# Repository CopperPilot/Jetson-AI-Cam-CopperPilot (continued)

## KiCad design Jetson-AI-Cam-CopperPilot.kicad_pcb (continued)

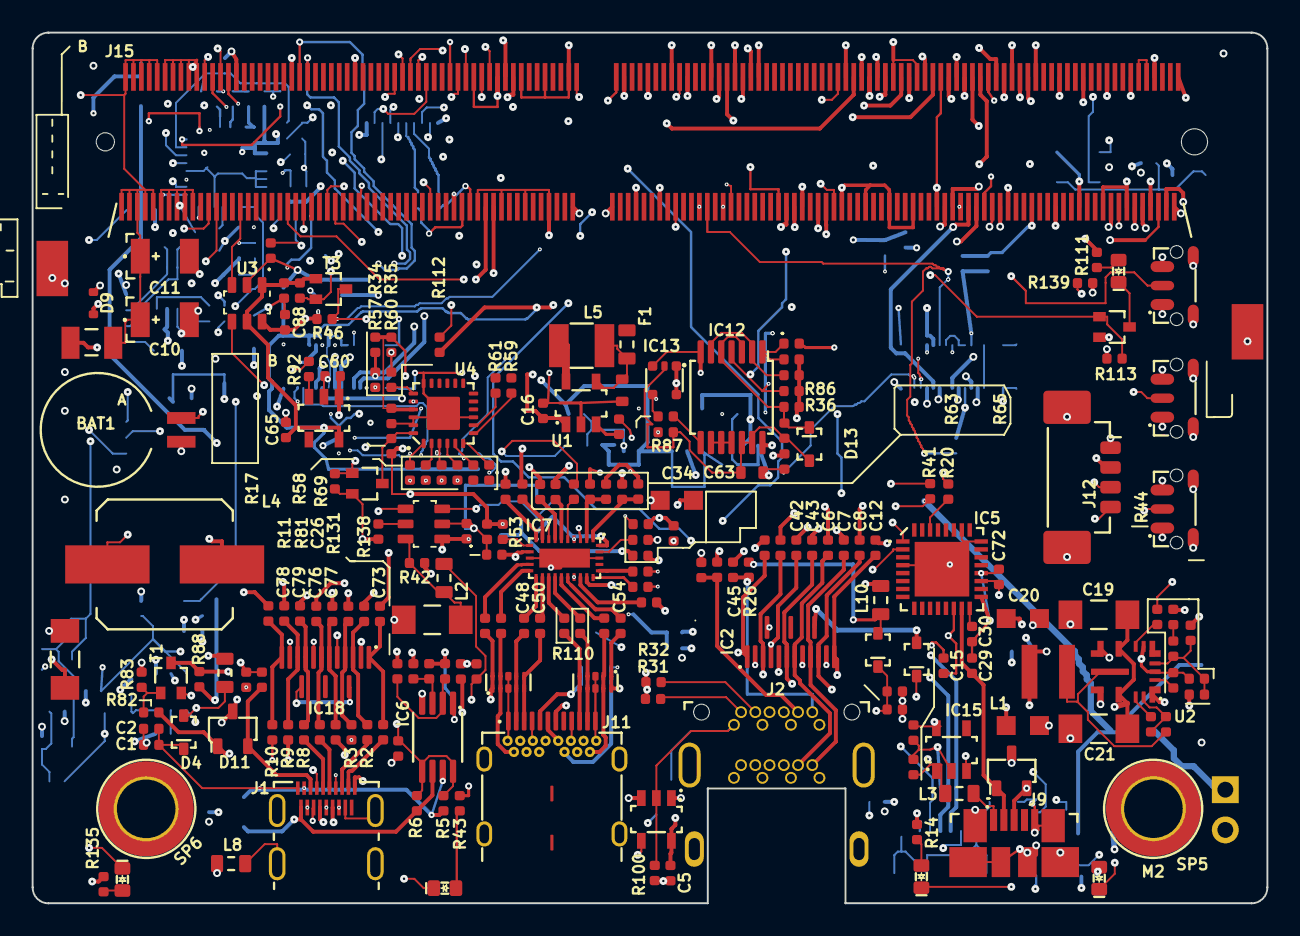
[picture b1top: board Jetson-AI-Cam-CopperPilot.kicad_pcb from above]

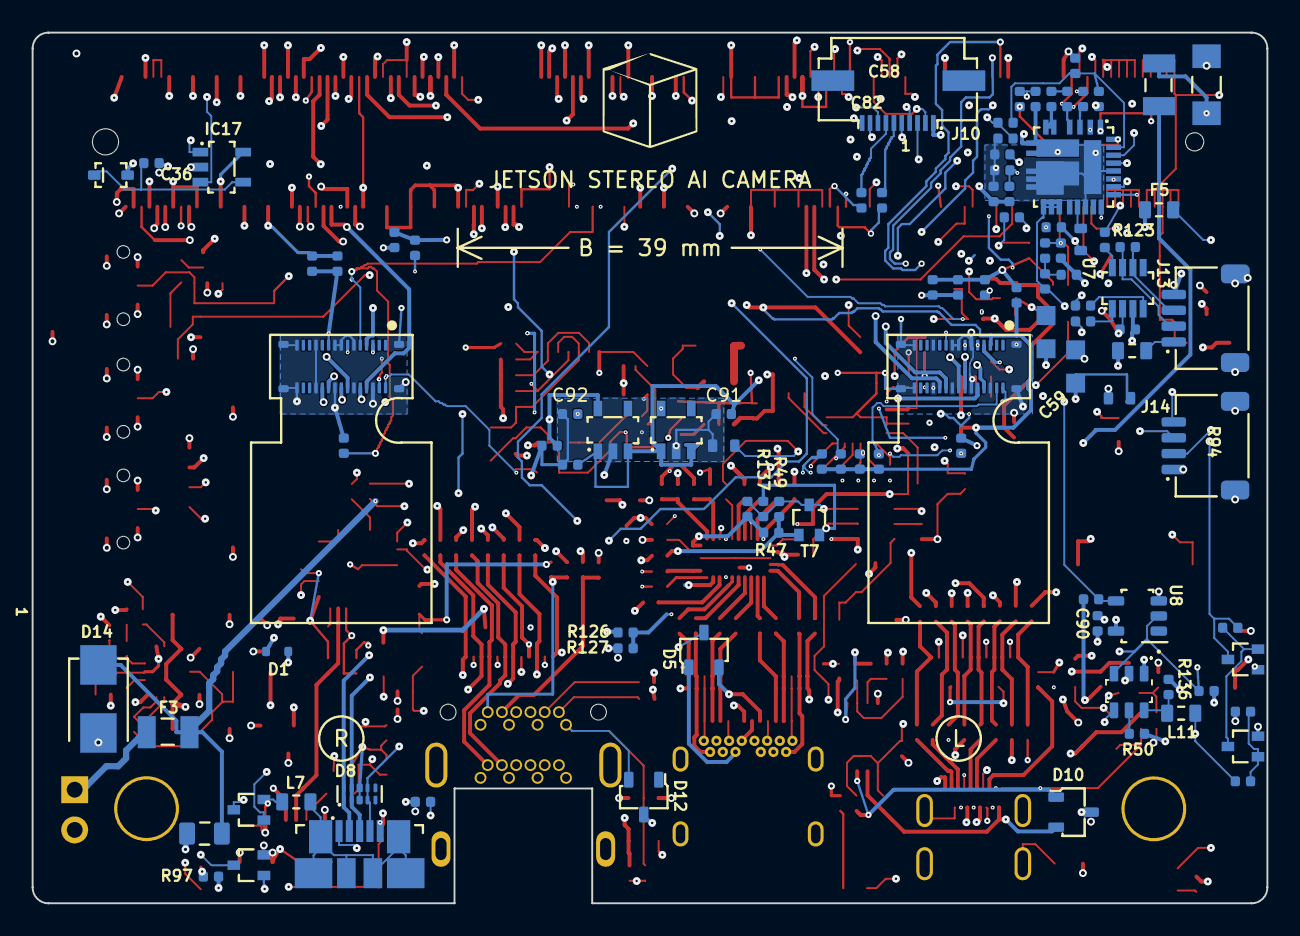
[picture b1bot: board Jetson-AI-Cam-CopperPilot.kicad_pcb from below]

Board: 8 copper layers, 78.0 x 55.0 mm, 305 parts (99 on the bottom side), 254 nets.

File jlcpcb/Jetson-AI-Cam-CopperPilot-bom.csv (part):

Designator,Value,Footprint,LCSC,MPN,DNP
BOOT1,LED_G_0603_LG_L29K-G2J1-24-Z,jetson-footprints:LED_0603_1608Metric_G,C72043,LG L29K-G2J1-24-Z,
C1,C_4u7_0402,jetson-footprints:C_0402_1005Metric,C23733,GRM155R61A475MEAAD,
C2,C_4u7_0402,jetson-footprints:C_0402_1005Metric,C23733,GRM155R61A475MEAAD,
C3,C_4u7_0402,jetson-footprints:C_0402_1005Metric,C23733,GRM155R61A475MEAAD,
C4,C_4u7_0402,jetson-footprints:C_0402_1005Metric,C23733,GRM155R61A475MEAAD,
C5,C_100n_0402,jetson-footprints:C_0402_1005Metric,C1525,GRM155R61H104KE14D,
C6,C_100n_0402,jetson-footprints:C_0402_1005Metric,C1525,GRM155R61H104KE14D,
C7,C_100n_0402,jetson-footprints:C_0402_1005Metric,C1525,GRM155R61H104KE14D,
C8,C_100n_0402,jetson-footprints:C_0402_1005Metric,C1525,GRM155R61H104KE14D,
C9,C_100n_0402,jetson-footprints:C_0402_1005Metric,C1525,GRM155R61H104KE14D,
C10,C_Pol_330u_6.3V_KEMET-T520-B,jetson-footprints:C_Pol_EIA-B,C134785,T520B337M006ATE040,
C11,C_Pol_330u_6.3V_KEMET-T520-B,jetson-footprints:C_Pol_EIA-B,C134785,T520B337M006ATE040,
C12,C_100n_0402,jetson-footprints:C_0402_1005Metric,C1525,GRM155R61H104KE14D,
C13,C_100n_0402,jetson-footprints:C_0402_1005Metric,C1525,GRM155R61H104KE14D,
C15,C_47p_0402,jetson-footprints:C_0402_1005Metric,C1548,C0402C470J5GACTU,
C17,C_10u_1206_50V,jetson-footprints:C_1206_3216Metric,C13585,C3216X7R1H106K160AE,
C19,C_10u_1206_50V,jetson-footprints:C_1206_3216Metric,C13585,C3216X7R1H106K160AE,
C20,C_47u_0805,jetson-footprints:C_0805_2012Metric,C16780,C0805C476M9PACTU,
C21,C_10u_1206_50V,jetson-footprints:C_1206_3216Metric,C13585,C3216X7R1H106K160AE,
C22,C_10u_1206_50V,jetson-footprints:C_1206_3216Metric,C13585,C3216X7R1H106K160AE,
C24,C_6p_0402,jetson-footprints:C_0402_1005Metric,C1571,0402N6R0D500CT,
C25,C_10u_0805,jetson-footprints:C_0805_2012Metric,C15850,160R15X106KV4E,
C26,C_100n_0402,jetson-footprints:C_0402_1005Metric,C1525,GRM155R61H104KE14D,
C27,C_100n_0402,jetson-footprints:C_0402_1005Metric,C1525,GRM155R61H104KE14D,
C29,C_47p_0402,jetson-footprints:C_0402_1005Metric,C1548,C0402C470J5GACTU,
C30,C_100n_0402,jetson-footprints:C_0402_1005Metric,C1525,GRM155R61H104KE14D,
C31,C_100u_1206,jetson-footprints:C_1206_3216Metric,C15068,GRM31CR60J107MEA8K,
C32,C_10u_0402,jetson-footprints:C_0402_1005Metric,C15525,CC0402MRX5R5BB106,
C33,C_100n_0402,jetson-footprints:C_0402_1005Metric,C1525,GRM155R61H104KE14D,
C34,C_47u_0805,jetson-footprints:C_0805_2012Metric,C16780,C0805C476M9PACTU,
C35,C_10u_0603,jetson-footprints:C_0603_1608Metric,C19702,GRM188R61A106KE69D,
C36,C_100n_0402,jetson-footprints:C_0402_1005Metric,C1525,GRM155R61H104KE14D,
C39,C_100n_0402,jetson-footprints:C_0402_1005Metric,C1525,GRM155R61H104KE14D,
C40,C_100n_0402,jetson-footprints:C_0402_1005Metric,C1525,GRM155R61H104KE14D,
C41,C_47n_0402,jetson-footprints:C_0402_1005Metric,C1536,GRM155R71C473KA01D,
C42,C_100n_0402,jetson-footprints:C_0402_1005Metric,C1525,GRM155R61H104KE14D,
C43,C_100n_0402,jetson-footprints:C_0402_1005Metric,C1525,GRM155R61H104KE14D,
C44,C_100n_0402,jetson-footprints:C_0402_1005Metric,C1525,GRM155R61H104KE14D,
C45,C_100n_0402,jetson-footprints:C_0402_1005Metric,C1525,GRM155R61H104KE14D,
C48,C_100n_0402,jetson-footprints:C_0402_1005Metric,C1525,GRM155R61H104KE14D,
C50,C_100n_0402,jetson-footprints:C_0402_1005Metric,C1525,GRM155R61H104KE14D,
C53,C_100n_0402,jetson-footprints:C_0402_1005Metric,C1525,GRM155R61H104KE14D,
C54,C_100n_0402,jetson-footprints:C_0402_1005Metric,C1525,GRM155R61H104KE14D,
C56,C_100n_50V_0402,jetson-footprints:C_0402_1005Metric,C307331,GRM155R71H104KE14D,
C57,C_100n_0402,jetson-footprints:C_0402_1005Metric,C1525,GRM155R61H104KE14D,
C58,C_33n_0402,jetson-footprints:C_0402_1005Metric,C1533,GCM155R71E333KA55D,
C59,C_47u_0805,jetson-footprints:C_0805_2012Metric,C16780,C0805C476M9PACTU,
C60,C_2u2_0402,jetson-footprints:C_0402_1005Metric,C12530,C1005X5R1A225K050BC,
C62,C_4u7_0402,jetson-footprints:C_0402_1005Metric,C23733,GRM155R61A475MEAAD,
C63,C_10u_0603,jetson-footprints:C_0603_1608Metric,C19702,GRM188R61A106KE69D,
C64,C_47u_0805,jetson-footprints:C_0805_2012Metric,C16780,C0805C476M9PACTU,
C65,C_1u_0402,jetson-footprints:C_0402_1005Metric,C52923,C1005X6S1A105K050BC,
C66,C_1u_0402,jetson-footprints:C_0402_1005Metric,C52923,C1005X6S1A105K050BC,
C67,C_2u2_0402,jetson-footprints:C_0402_1005Metric,C12530,C1005X5R1A225K050BC,
C71,C_100n_0402,jetson-footprints:C_0402_1005Metric,C1525,GRM155R61H104KE14D,
C72,C_100n_0402,jetson-footprints:C_0402_1005Metric,C1525,GRM155R61H104KE14D,
C73,C_100n_0402,jetson-footprints:C_0402_1005Metric,C1525,GRM155R61H104KE14D,
C74,C_100n_0402,jetson-footprints:C_0402_1005Metric,C1525,GRM155R61H104KE14D,
C75,C_100n_0402,jetson-footprints:C_0402_1005Metric,C1525,GRM155R61H104KE14D,
C76,C_100n_0402,jetson-footprints:C_0402_1005Metric,C1525,GRM155R61H104KE14D,
C77,C_100n_0402,jetson-footprints:C_0402_1005Metric,C1525,GRM155R61H104KE14D,
C78,C_100n_0402,jetson-footprints:C_0402_1005Metric,C1525,GRM155R61H104KE14D,
C79,C_100n_0402,jetson-footprints:C_0402_1005Metric,C1525,GRM155R61H104KE14D,
C80,C_100n_0402,jetson-footprints:C_0402_1005Metric,C1525,GRM155R61H104KE14D,
C81,C_10u_0603,jetson-footprints:C_0603_1608Metric,C19702,GRM188R61A106KE69D,
C83,C_100n_0402,jetson-footprints:C_0402_1005Metric,C1525,GRM155R61H104KE14D,
C84,C_1u_0402,jetson-footprints:C_0402_1005Metric,C52923,C1005X6S1A105K050BC,
C85,C_4u7_0603,jetson-footprints:C_0603_1608Metric,C19666,C1608X5R1V475M080AC,
C86,C_100n_0402,jetson-footprints:C_0402_1005Metric,C1525,GRM155R61H104KE14D,
C87,C_1u_0402,jetson-footprints:C_0402_1005Metric,C52923,C1005X6S1A105K050BC,
C88,C_100n_0402,jetson-footprints:C_0402_1005Metric,C1525,GRM155R61H104KE14D,
C89,C_100n_0402,jetson-footprints:C_0402_1005Metric,C1525,GRM155R61H104KE14D,
C90,C_100n_0402,jetson-footprints:C_0402_1005Metric,C1525,GRM155R61H104KE14D,
C91,1uF_0402,jetson-footprints:C_0402_1005Metric,C52923,C1005X6S1A105K050BC,
C92,2.2uF_0402,jetson-footprints:C_0402_1005Metric,C12530,C1005X5R1A225K050BC,
C93,1uF_0402,jetson-footprints:C_0402_1005Metric,C52923,C1005X6S1A105K050BC,
C94,2.2uF_0402,jetson-footprints:C_0402_1005Metric,C12530,C1005X5R1A225K050BC,
C95,C_100n_0402,jetson-footprints:C_0402_1005Metric,C1525,GRM155R61H104KE14D,
C96,C_100n_0402,jetson-footprints:C_0402_1005Metric,C1525,GRM155R61H104KE14D,
C97,C_100n_0402,jetson-footprints:C_0402_1005Metric,C1525,GRM155R61H104KE14D,
C98,C_2u2_0402,jetson-footprints:C_0402_1005Metric,C12530,C1005X5R1A225K050BC,
C99,C_100n_0402,jetson-footprints:C_0402_1005Metric,C1525,GRM155R61H104KE14D,
C100,C_100n_0402,jetson-footprints:C_0402_1005Metric,C1525,GRM155R61H104KE14D,
C101,C_100n_0402,jetson-footprints:C_0402_1005Metric,C1525,GRM155R61H104KE14D,
C102,C_2u2_0402,jetson-footprints:C_0402_1005Metric,C12530,C1005X5R1A225K050BC,
C103,C_100n_0402,jetson-footprints:C_0402_1005Metric,C1525,GRM155R61H104KE14D,
C104,C_100n_0402,jetson-footprints:C_0402_1005Metric,C1525,GRM155R61H104KE14D,
CAM_L,IMX219_30P,jetson-footprints:Camera_Module_IMX219-D160,C424662,BM20B(0.8)-30DS-0.4V(51),
CAM_R,IMX219_30P,jetson-footprints:Camera_Module_IMX219-D160,C424662,BM20B(0.8)-30DS-0.4V(51),
D1,ESD5B5_0ST1G,jetson-footprints:SOD-523_NP,C15906,ESD5B5.0ST1G,
D2,B0520W,jetson-footprints:D_SOD-323F,C8598,B0520W,
D3,PESD2USB5UV-TR,jetson-footprints:SOT-23-3,C2827695,PESD2USB5UV-TR,
D4,B0520W,jetson-footprints:D_SOD-323F,C8598,B0520W,
D5,PESD2USB5UV-TR,jetson-footprints:SOT-23-3,C2827695,PESD2USB5UV-TR,
D6,TPD4E05U06QDQARQ1,jetson-footprints:USON-10_2.5x1mm_P0.5mm,C138252,TPD4E05U06QDQARQ1,
D7,TPD4E05U06QDQARQ1,jetson-footprints:USON-10_2.5x1mm_P0.5mm,C138252,TPD4E05U06QDQARQ1,
D8,TPD4E05U06QDQARQ1,jetson-footprints:USON-10_2.5x1mm_P0.5mm,C138252,TPD4E05U06QDQARQ1,
D9,ESD5B5_0ST1G,jetson-footprints:SOD-523_NP,C15906,ESD5B5.0ST1G,
D10,PESD2USB5UV-TR,jetson-footprints:SOT-23-3,C2827695,PESD2USB5UV-TR,
D11,PESD2USB5UV-TR,jetson-footprints:SOT-23-3,C2827695,PESD2USB5UV-TR,
D12,PESD2USB5UV-TR,jetson-footprints:SOT-23-3,C2827695,PESD2USB5UV-TR,
D13,1N4148WS,jetson-footprints:D_SOD-323F,C2128,1N4148WS,
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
